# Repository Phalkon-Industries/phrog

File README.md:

# phrog
Super low cost spectrophotometric ph sensor

What is the purpose of the pHrog?

To be an educational kit that people can build themselves and use to learn how to make a spectrophotometric measurement.

It should be able to do basic spectrophotometric measuremtns and be able to get pH to +-0.1 units. That is the goal. 

It should be easy to build, and be repairable.

Still under early development

## Repository layout

| Folder | Contents |
|--------|----------|
| `phrog-mainboard/` | KiCad project, datasheets, and production outputs for the mainboard. |
| `enclosure/` | FreeCAD enclosure model. |
| `firmware/` | PlatformIO firmware for the nRF52840 Pro Micro (see `firmware/README.md`). |

## License

This project is licensed under the CERN Open Hardware Licence Version 2 - Strongly Reciprocal
(`CERN-OHL-S-2.0`). See [`LICENSE`](LICENSE) for the full text.

Source Location: https://github.com/Phalkon-Industries/phrog

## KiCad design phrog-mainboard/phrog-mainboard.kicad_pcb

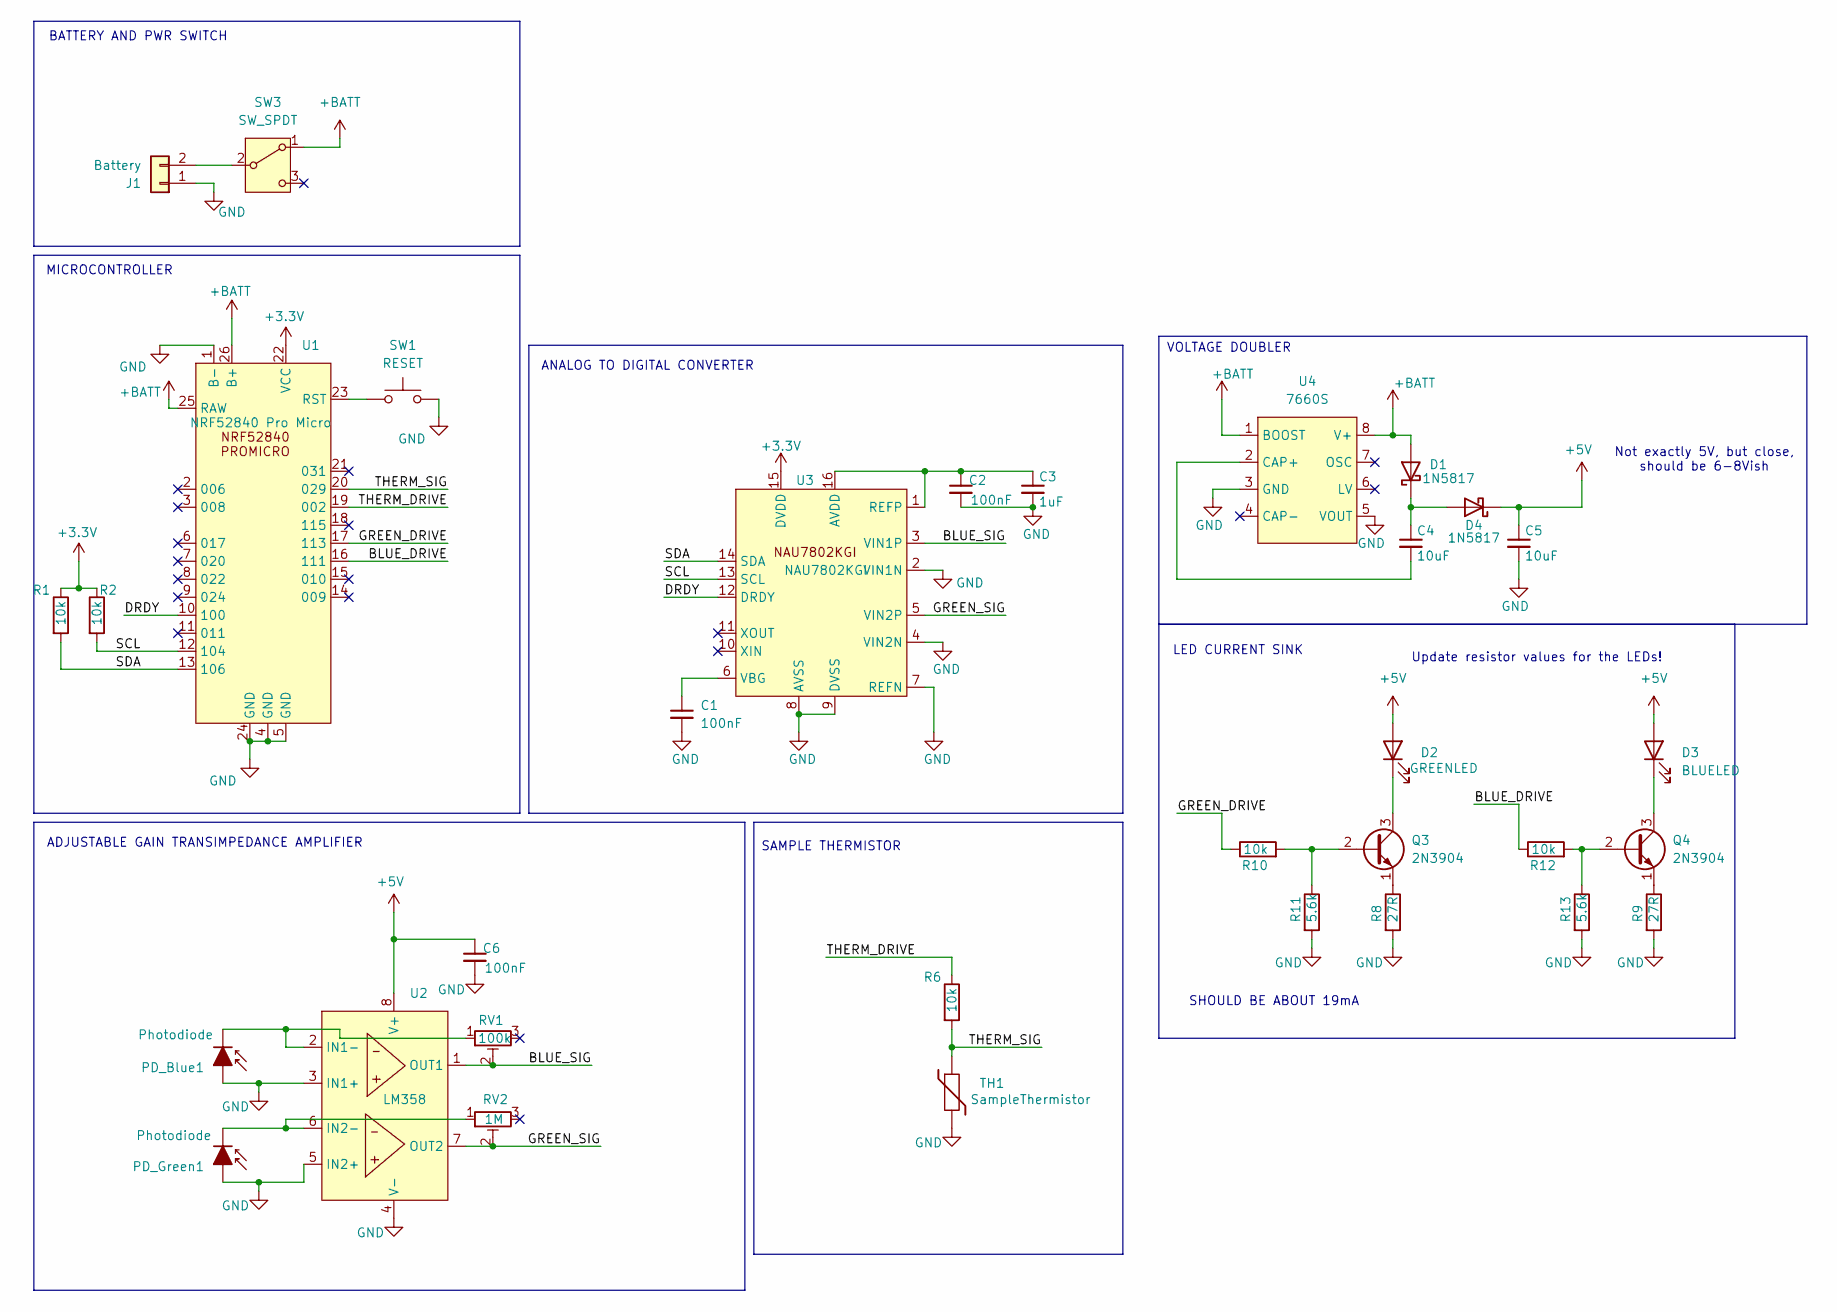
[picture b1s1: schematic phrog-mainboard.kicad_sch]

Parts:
C1, C2, C6: 100nF; C_Disc_D4.3mm_W1.9mm_P5.00mm
C3: 1uF; C_Disc_D4.3mm_W1.9mm_P5.00mm
C4, C5: 10uF; C_Disc_D4.3mm_W1.9mm_P5.00mm
D1, D4: 1N5817; D_DO-41_SOD81_P10.16mm_Horizontal
D2: GREENLED; LED_D5.0mm_Horizontal_O1.27mm_Z3.0mm
D3: BLUELED; LED_D5.0mm_Horizontal_O1.27mm_Z3.0mm
J1: Battery; JST_PH_B2B-PH-K_1x02_P2.00mm_Vertical
PD_Blue1: Photodiode; PD_Vertical
PD_Green1: Photodiode; PD_Vertical
Q3, Q4: 2N3904; TO-92_Inline
R1, R2, R6, R10, R12: 10k; R_Axial_DIN0207_L6.3mm_D2.5mm_P10.16mm_Horizontal
R8, R9: 27R; R_Axial_DIN0207_L6.3mm_D2.5mm_P10.16mm_Horizontal
R11, R13: 5.6k; R_Axial_DIN0207_L6.3mm_D2.5mm_P10.16mm_Horizontal
RV1: 100k; Potentiometer_Bourns_3296W_Vertical
RV2: 1M; Potentiometer_Bourns_3296W_Vertical
SW1: RESET; SW_PUSH_6mm
SW3: SW_SPDT; SW_Slide-03_Wuerth-WS-SLTV_10x2.5x6.4_P2.54mm
TH1: SampleThermistor; Thermistor_Wire
U1: NRF52840 Pro Micro; nrf52840_pro_micro
U2: LM358; DIP-8_W7.62mm_LongPads
U3: NAU7802KGI; DIP-16_W7.62mm_LongPads
U4: 7660S; DIP-8_W7.62mm_LongPads

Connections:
+3.3V: R1.1, R2.1, U1.22 (VCC), U3.15 (DVDD)
+5V: C5.1, C6.1, D2.2 (A), D3.2 (A), D4.1 (K), U2.8 (V+)
+BATT: D1.2 (A), SW3.1 (A), U1.25 (RAW), U1.26 (B+), U4.1 (BOOST), U4.8 (V+)
/BLUE_DRIVE: R12.1, U1.16 (111)
/BLUE_SIG: RV1.2, U2.1 (OUT1), U3.3 (VIN1P)
/DRDY: U1.10 (100), U3.12 (DRDY)
/GREEN_DRIVE: R10.1, U1.17 (113)
/GREEN_SIG: RV2.2, U2.7 (OUT2), U3.5 (VIN2P)
/SCL: R2.2, U1.12 (104), U3.13 (SCL)
/SDA: R1.2, U1.13 (106), U3.14 (SDA)
/THERM_DRIVE: R6.1, U1.19 (002)
/THERM_SIG: R6.2, TH1.1, U1.20 (029)
GND: C1.2, C2.2, C3.2, C5.2, C6.2, J1.1, PD_Blue1.2 (A), PD_Green1.2 (A), R8.2, R9.2, R11.2, R13.2, SW1.2, TH1.2, U1.1 (B-), U1.4 (GND), U1.5 (GND), U1.24 (GND), U2.3 (IN1+), U2.4 (V-), U2.5 (IN2+), U3.2 (VIN1N), U3.4 (VIN2N), U3.7 (REFN), U3.8 (AVSS), U3.9 (DVSS), U4.3 (GND), U4.5 (VOUT)
unnamed: C4.1, D1.1 (K), D4.2 (A)
unnamed: D2.1 (K), Q3.3 (C)
unnamed: D3.1 (K), Q4.3 (C)
unnamed: J1.2, SW3.2 (B)
unnamed: PD_Blue1.1 (K), RV1.1, U2.2 (IN1-)
unnamed: PD_Green1.1 (K), RV2.1, U2.6 (IN2-)
unnamed: Q3.2 (B), R10.2, R11.1
unnamed: Q3.1 (E), R8.1
unnamed: Q4.2 (B), R12.2, R13.1
unnamed: Q4.1 (E), R9.1
unnamed: SW1.1, U1.23 (RST)
unnamed: C2.1, C3.1, U3.1 (REFP), U3.16 (AVDD)
unnamed: C1.1, U3.6 (VBG)
unnamed: C4.2, U4.2 (CAP+)

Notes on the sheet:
Not exactly 5V, but close, should be 6-8Vish
SHOULD BE ABOUT 19mA
VOLTAGE DOUBLER
LED CURRENT SINK
SAMPLE THERMISTOR
BATTERY AND PWR SWITCH
ADJUSTABLE GAIN TRANSIMPEDANCE AMPLIFIER
MICROCONTROLLER
Update resistor values for the LEDs!
ANALOG TO DIGITAL CONVERTER

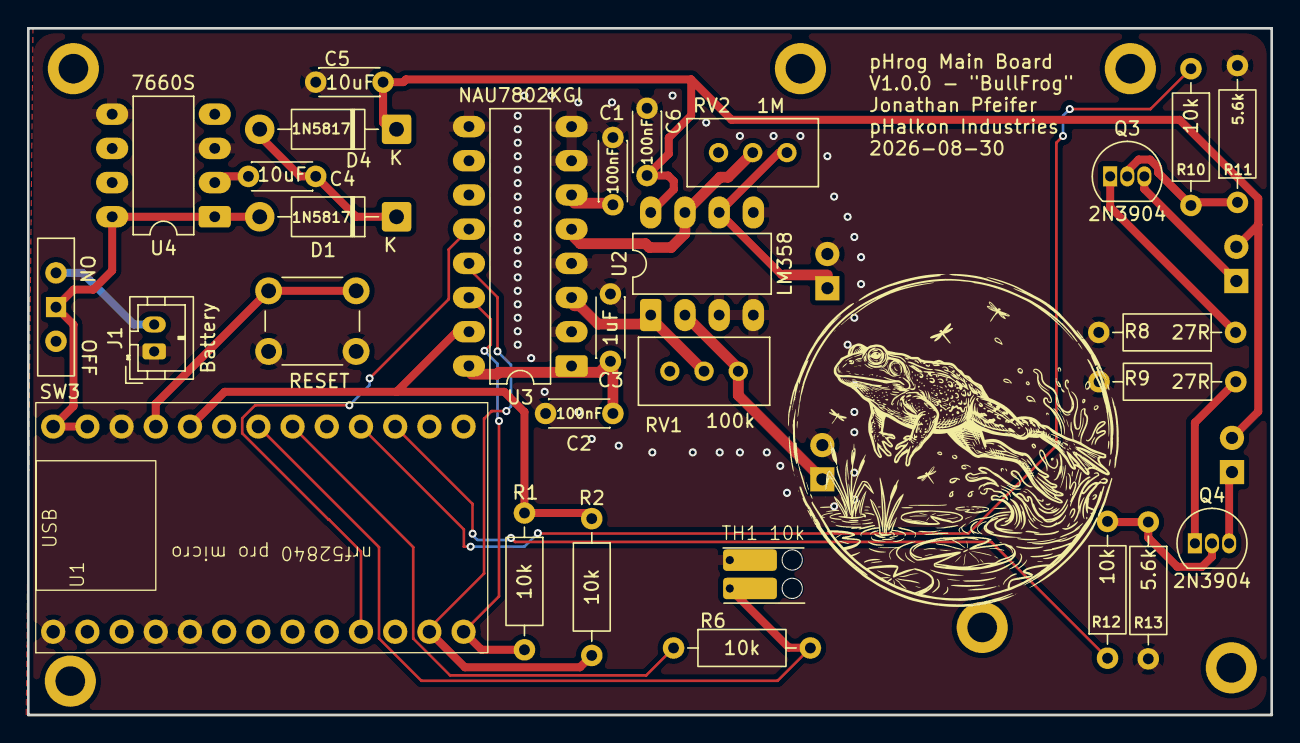
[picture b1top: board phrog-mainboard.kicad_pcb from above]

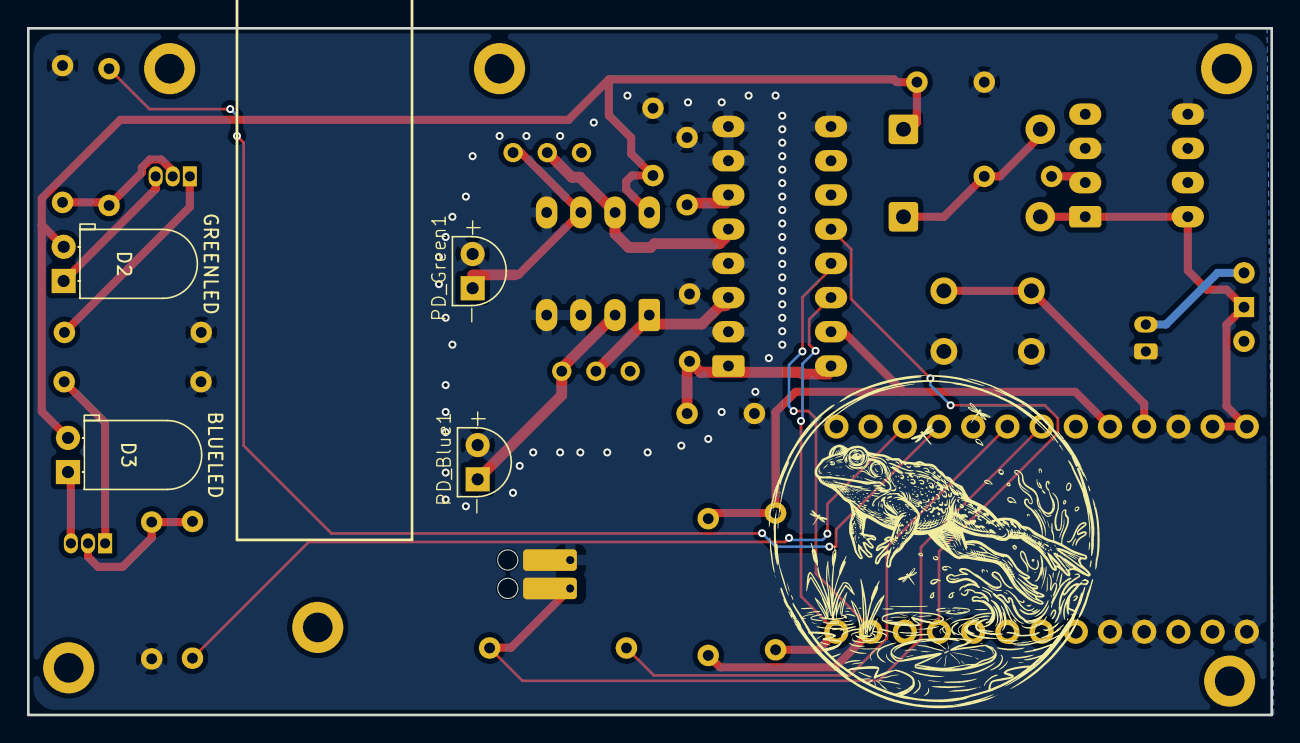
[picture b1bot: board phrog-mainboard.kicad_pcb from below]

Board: 2 copper layers, 92.4 x 51.0 mm, 33 parts (4 on the bottom side), 27 nets.

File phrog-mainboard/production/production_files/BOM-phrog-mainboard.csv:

Comment,Designator,Footprint,LCSC,Quantity
27R,R8,R_Axial_DIN0207_L6.3mm_D2.5mm_P10.16mm_Horizontal,,1
10k,R6,R_Axial_DIN0207_L6.3mm_D2.5mm_P10.16mm_Horizontal,,1
BLUELED,D3,LED_D5.0mm_Horizontal_O1.27mm_Z3.0mm,,1
Photodiode,PD_Blue1,PD_Vertical,,1
1N5817,D4,D_DO-41_SOD81_P10.16mm_Horizontal,,1
NRF52840 Pro Micro,U1,nrf52840_pro_micro,,1
100k,RV1,Potentiometer_Bourns_3296W_Vertical,,1
100nF,C2,C_Disc_D4.3mm_W1.9mm_P5.00mm,,1
SW_SPDT,SW3,SW_Slide-03_Wuerth-WS-SLTV_10x2.5x6.4_P2.54mm,,1
SampleThermistor,TH1,Thermistor_Wire,,1
100nF,C1,C_Disc_D4.3mm_W1.9mm_P5.00mm,,1
2N3904,Q4,TO-92_Inline,,1
10k,R2,R_Axial_DIN0207_L6.3mm_D2.5mm_P10.16mm_Horizontal,,1
RESET,SW1,SW_PUSH_6mm,,1
10uF,C5,C_Disc_D4.3mm_W1.9mm_P5.00mm,,1
100nF,C6,C_Disc_D4.3mm_W1.9mm_P5.00mm,,1
10k,R10,R_Axial_DIN0207_L6.3mm_D2.5mm_P10.16mm_Horizontal,,1
1uF,C3,C_Disc_D4.3mm_W1.9mm_P5.00mm,,1
5.6k,R13,R_Axial_DIN0207_L6.3mm_D2.5mm_P10.16mm_Horizontal,,1
2N3904,Q3,TO-92_Inline,,1
27R,R9,R_Axial_DIN0207_L6.3mm_D2.5mm_P10.16mm_Horizontal,,1
10k,R1,R_Axial_DIN0207_L6.3mm_D2.5mm_P10.16mm_Horizontal,,1
1N5817,D1,D_DO-41_SOD81_P10.16mm_Horizontal,,1
10k,R12,R_Axial_DIN0207_L6.3mm_D2.5mm_P10.16mm_Horizontal,,1
1M,RV2,Potentiometer_Bourns_3296W_Vertical,,1
Battery,J1,JST_PH_B2B-PH-K_1x02_P2.00mm_Vertical,,1
5.6k,R11,R_Axial_DIN0207_L6.3mm_D2.5mm_P10.16mm_Horizontal,,1
7660S,U4,DIP-8_W7.62mm_LongPads,,1
Photodiode,PD_Green1,PD_Vertical,,1
GREENLED,D2,LED_D5.0mm_Horizontal_O1.27mm_Z3.0mm,,1
LM358,U2,DIP-8_W7.62mm_LongPads,,1
10uF,C4,C_Disc_D4.3mm_W1.9mm_P5.00mm,,1
NAU7802KGI,U3,DIP-16_W7.62mm_LongPads,,1
